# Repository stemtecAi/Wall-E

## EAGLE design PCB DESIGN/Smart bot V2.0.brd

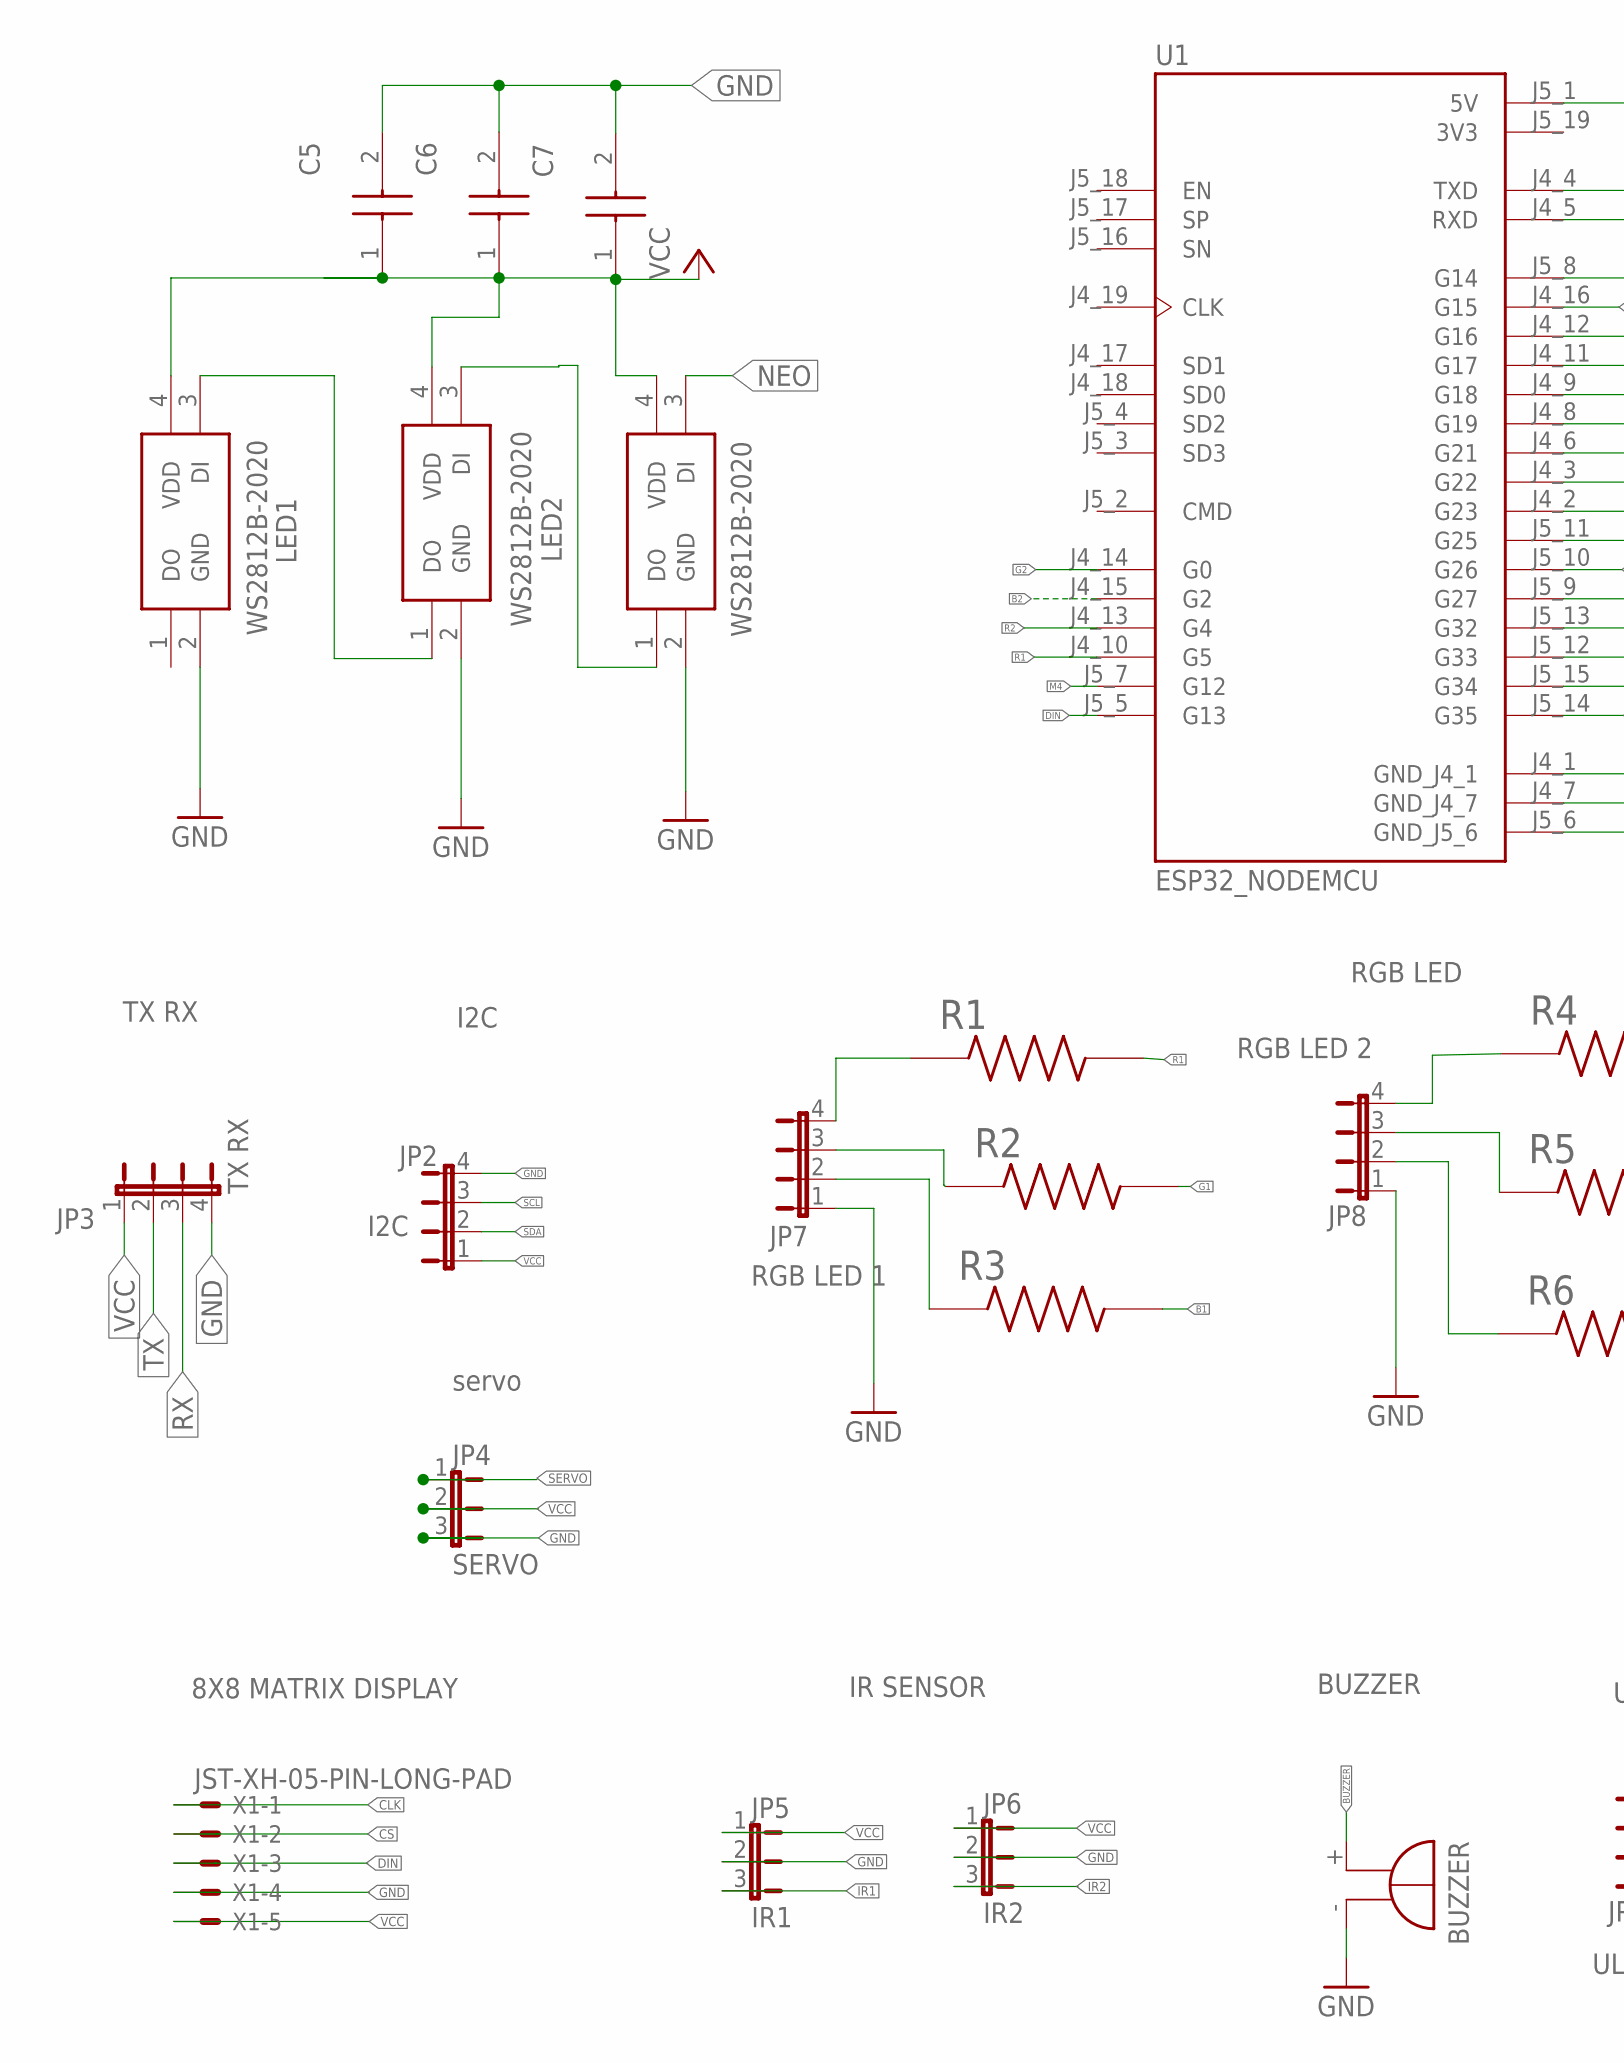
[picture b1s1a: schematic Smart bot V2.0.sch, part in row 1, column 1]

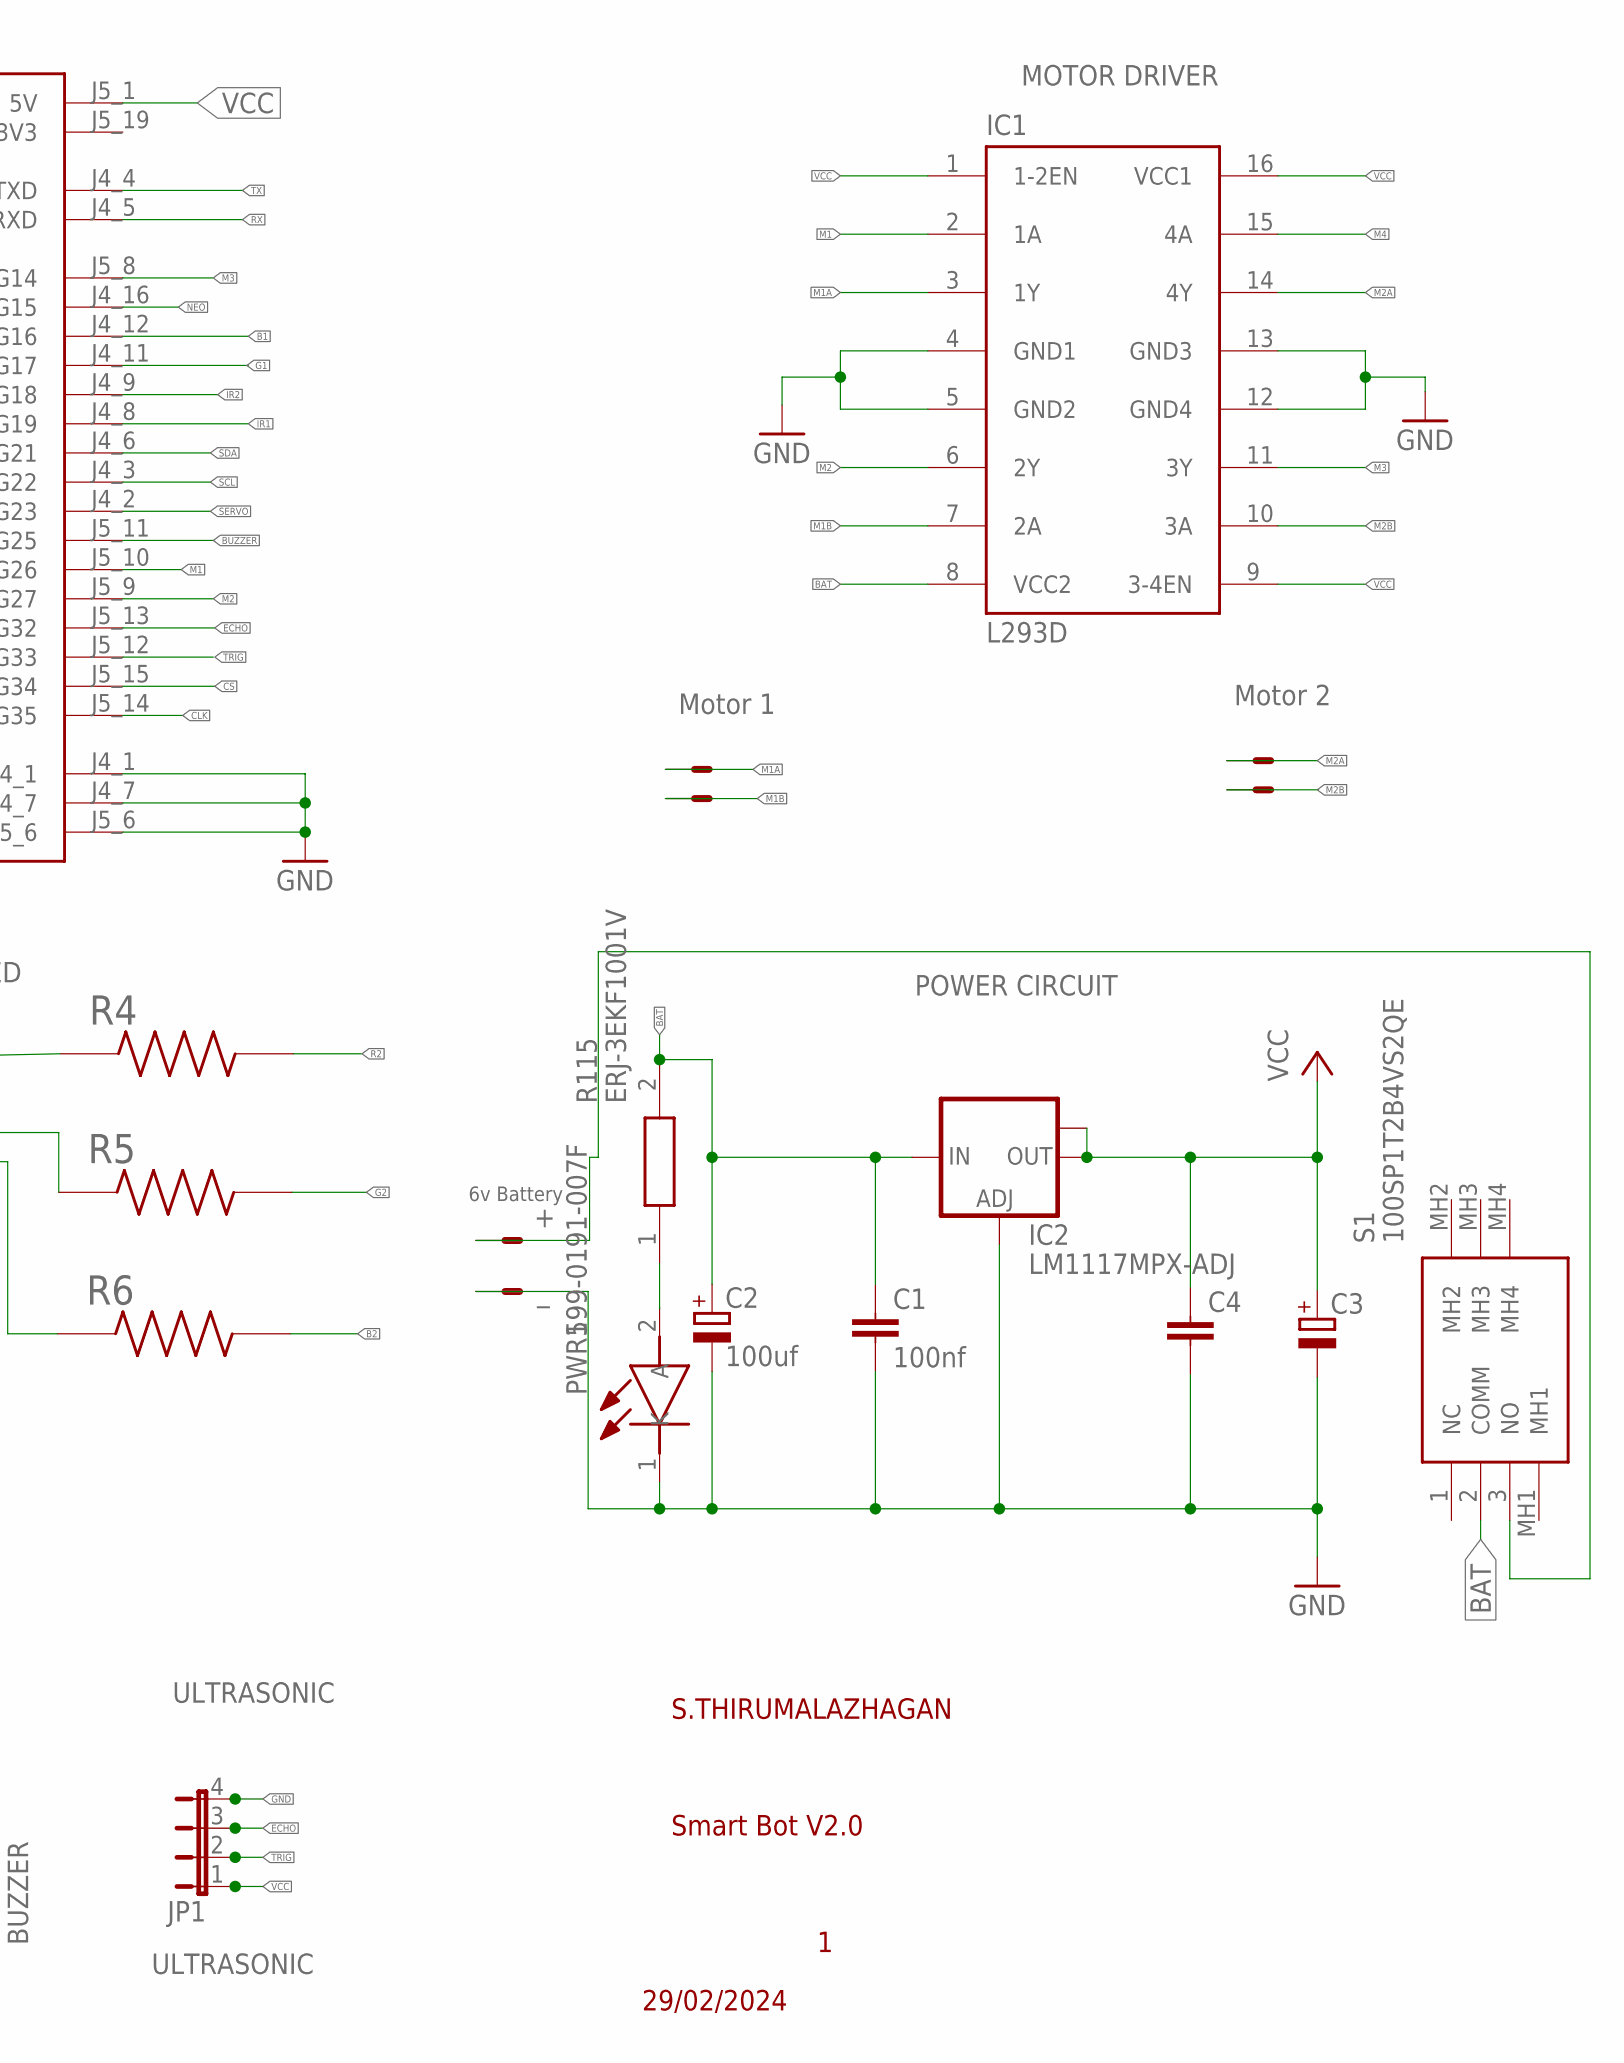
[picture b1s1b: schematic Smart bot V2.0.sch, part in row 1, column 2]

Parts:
6V: JST-XH-02-PIN-LONG-PAD; JST-XH-02-PACKAGE-LONG-PAD
BUZZER: F/HMB
C1: 100nf; C1206
C2: 100uf; SMC_B
C3: CPOL-EUSMCB; SMC_B
C4: C-EUC1206; C1206
C5, C6, C7: C0805X102KMRECAUTO7210; CAPC2012X98N
IC1: L293D; DIL16
IC2: LM1117MPX-ADJ; SOT223
JP1: ULTRASONIC; JP4
JP2: I2C; JP4
JP3: TX RX; JP4
JP4: SERVO; JP2
JP5: IR1; JP2
JP6: IR2; JP2
JP7: RGB LED 1; JP4
JP8: RGB LED 2; JP4
LED1, LED2, LED3: WS2812B-2020; WS2812B2020
PWR1: 599-0191-007F; LEDC2012X90N
R1, R2, R3, R4, R5, R6: RR0306P-101-D; RESC0603X26N
R115: ERJ-3EKF1001V; RESC1608X55N
S1: 100SP1T2B4VS2QE
U1: ESP32_NODEMCU; MODULE_ESP32_NODEMCU
X1: JST-XH-05-PIN-LONG-PAD; JST-XH-05-PACKAGE-LONG-PAD
X2, X3: JST-XH-02-PIN-LONG-PAD; JST-XH-02-PACKAGE-LONG-PAD

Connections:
3V3: U1.J5_19 (3V3)
6V: 6V.1, S1.3 (NO)
B1: R3.2, U1.J4_12 (G16)
B2: R6.2, U1.J4_15 (G2)
BAT: C1.1, C2.+, IC1.8 (VCC2), IC2.3 (IN), R115.2, S1.2 (COMM)
BUZZER: BUZZER.+, U1.J5_11 (G25)
CLK: U1.J5_14 (G35), X1.1
CS: U1.J5_15 (G34), X1.2
DIN: U1.J5_5 (G13), X1.3
ECHO: JP1.3, U1.J5_13 (G32)
G1: R2.2, U1.J4_11 (G17)
G2: R5.2, U1.J4_14 (G0)
GND: 6V.2, BUZZER.-, C1.2, C2.-, C3.-, C4.2, C5.2, C6.2, C7.2, IC1.4 (GND1), IC1.5 (GND2), IC1.12 (GND4), IC1.13 (GND3), IC2.1 (ADJ), JP1.4, JP2.4, JP3.4, JP4.3, JP5.2, JP6.2, JP7.1, JP8.1, LED1.2 (GND), LED2.2 (GND), LED3.2 (GND), PWR1.1 (K), U1.J4_1 (GND_J4_1), U1.J4_7 (GND_J4_7), U1.J5_6 (GND_J5_6), X1.4
IR1: JP5.3, U1.J4_8 (G19)
IR2: JP6.3, U1.J4_9 (G18)
M1: IC1.2 (1A), U1.J5_10 (G26)
M1A: IC1.3 (1Y), X2.1
M1B: IC1.7 (2A), X2.2
M2: IC1.6 (2Y), U1.J5_9 (G27)
M2A: IC1.14 (4Y), X3.1
M2B: IC1.10 (3A), X3.2
M3: IC1.11 (3Y), U1.J5_8 (G14)
M4: IC1.15 (4A), U1.J5_7 (G12)
unnamed: JP7.4, R1.1
unnamed: JP7.3, R2.1
unnamed: JP7.2, R3.1
unnamed: JP8.4, R4.1
unnamed: JP8.3, R5.1
unnamed: JP8.2, R6.1
unnamed: PWR1.2 (A), R115.1
unnamed: LED1.3 (DI), LED2.1 (DO)
unnamed: LED2.3 (DI), LED3.1 (DO)
NEO: LED3.3 (DI), U1.J4_16 (G15)
R1: R1.2, U1.J4_10 (G5)
R2: R4.2, U1.J4_13 (G4)
RX: JP3.3, U1.J4_5 (RXD)
SCL: JP2.3, U1.J4_3 (G22)
SDA: JP2.2, U1.J4_6 (G21)
SERVO: JP4.1, U1.J4_2 (G23)
TRIG: JP1.2, U1.J5_12 (G33)
TX: JP3.2, U1.J4_4 (TXD)
VCC: C3.+, C4.1, C5.1, C6.1, C7.1, IC1.1 (1-2EN), IC1.9 (3-4EN), IC1.16 (VCC1), IC2.2 (OUT), IC2.TAB (OUT1), JP1.1, JP2.1, JP3.1, JP4.2, JP5.1, JP6.1, LED1.4 (VDD), LED2.4 (VDD), LED3.4 (VDD), U1.J5_1 (5V), X1.5

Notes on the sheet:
Smart Bot V2.0
29/02/2024
S.THIRUMALAZHAGAN
MOTOR DRIVER
RGB LED
BUZZER
POWER CIRCUIT
Motor 1
Motor 2
6v Battery
I2C
IR SENSOR
8X8 MATRIX DISPLAY
ULTRASONIC
TX RX
servo

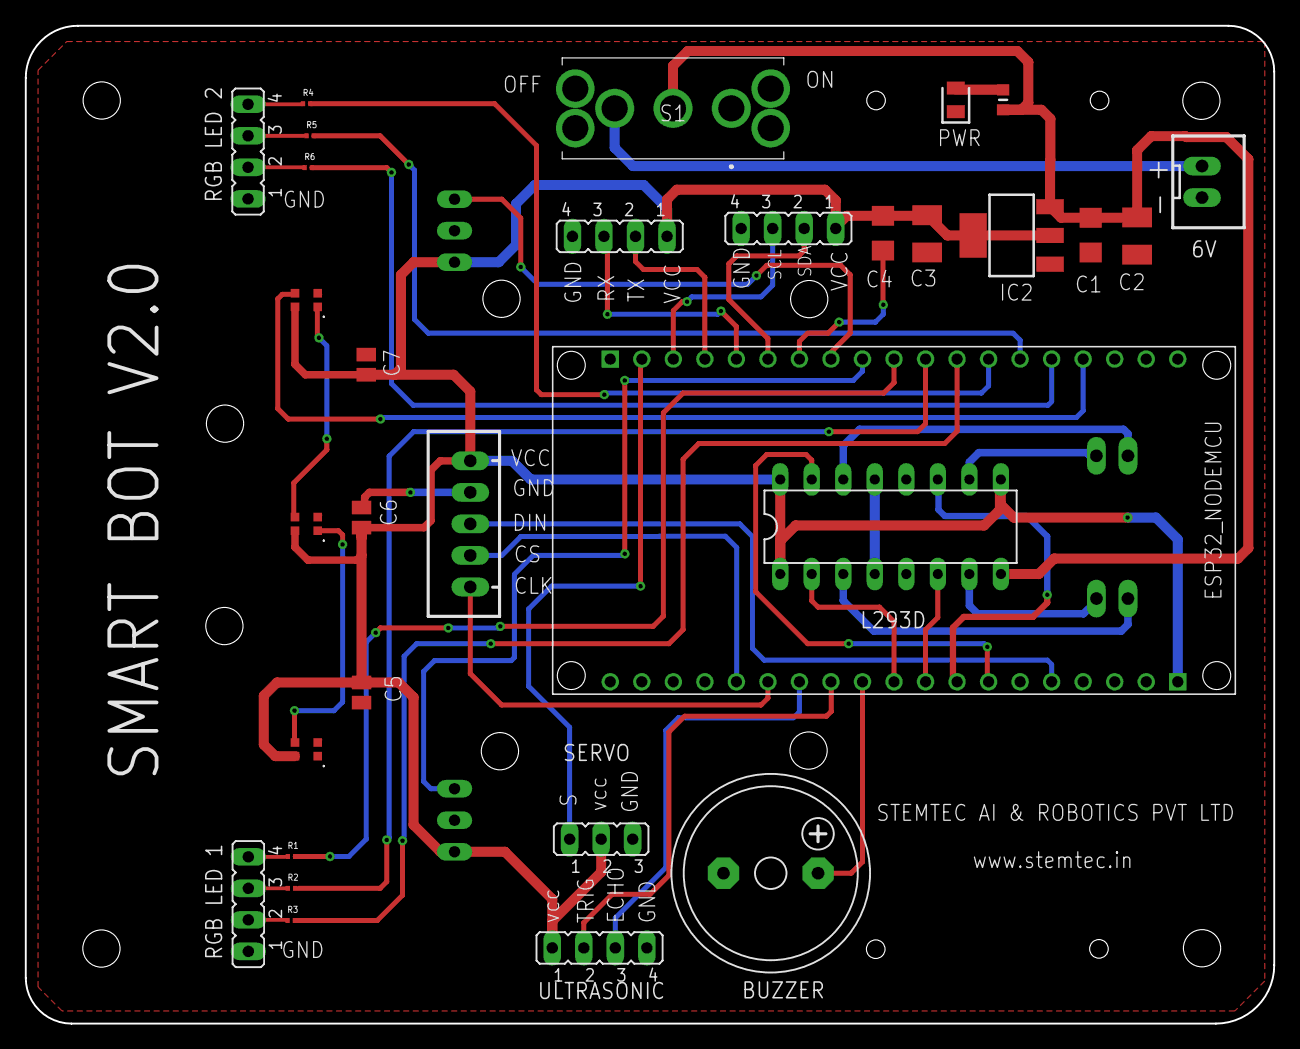
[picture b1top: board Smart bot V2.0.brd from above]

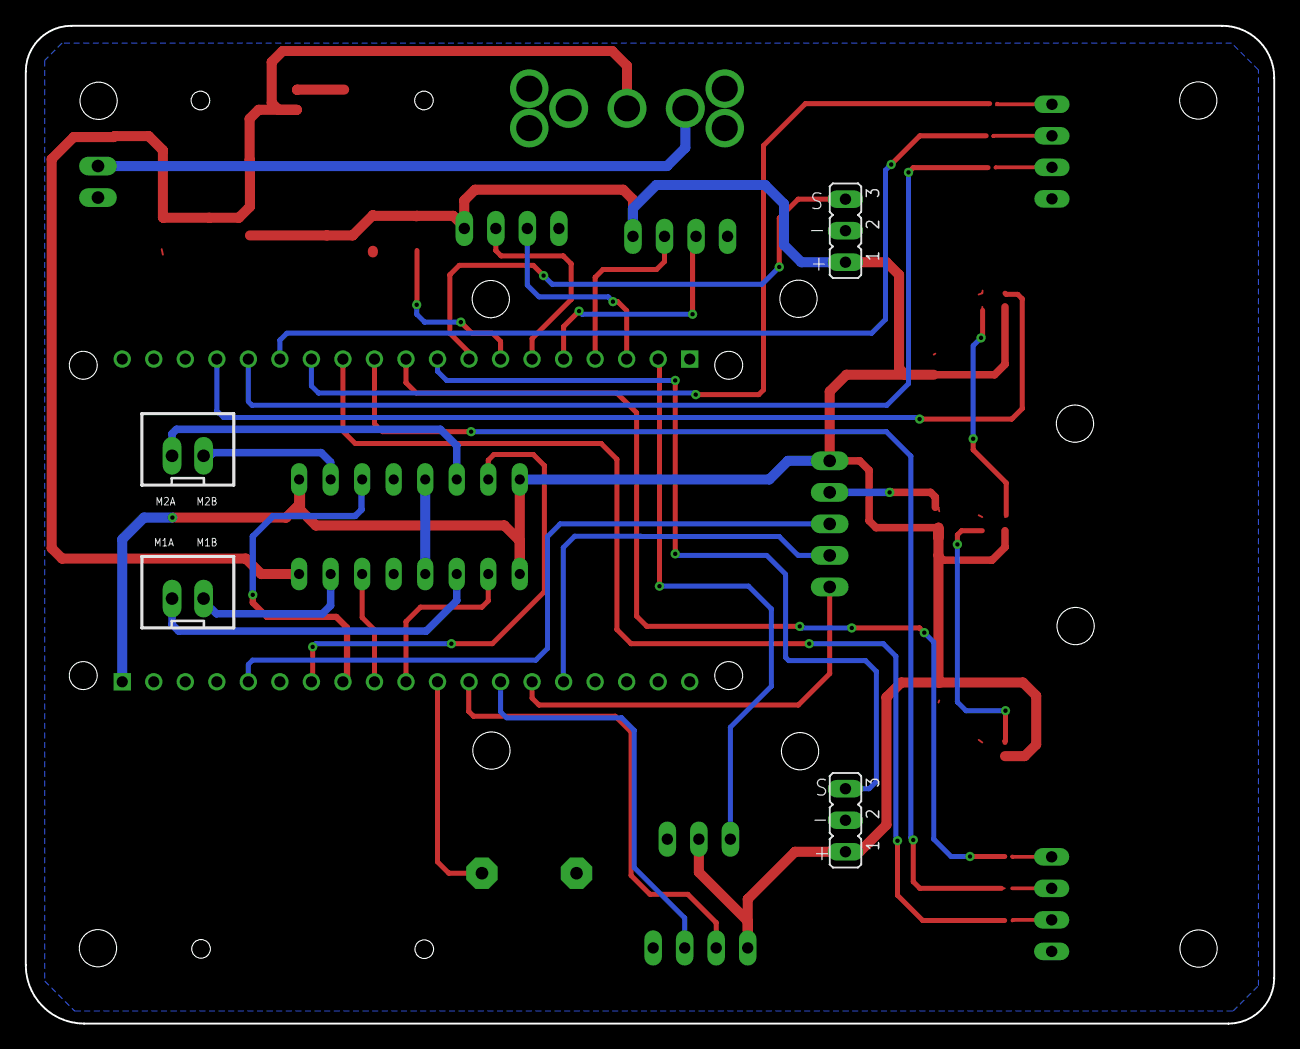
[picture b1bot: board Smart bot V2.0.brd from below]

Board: 2 copper layers, 100.6 x 80.4 mm, 35 parts (4 on the bottom side), 41 nets.

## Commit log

2024-04-02 PCB DESIGN OF SMART BOT V2.0
